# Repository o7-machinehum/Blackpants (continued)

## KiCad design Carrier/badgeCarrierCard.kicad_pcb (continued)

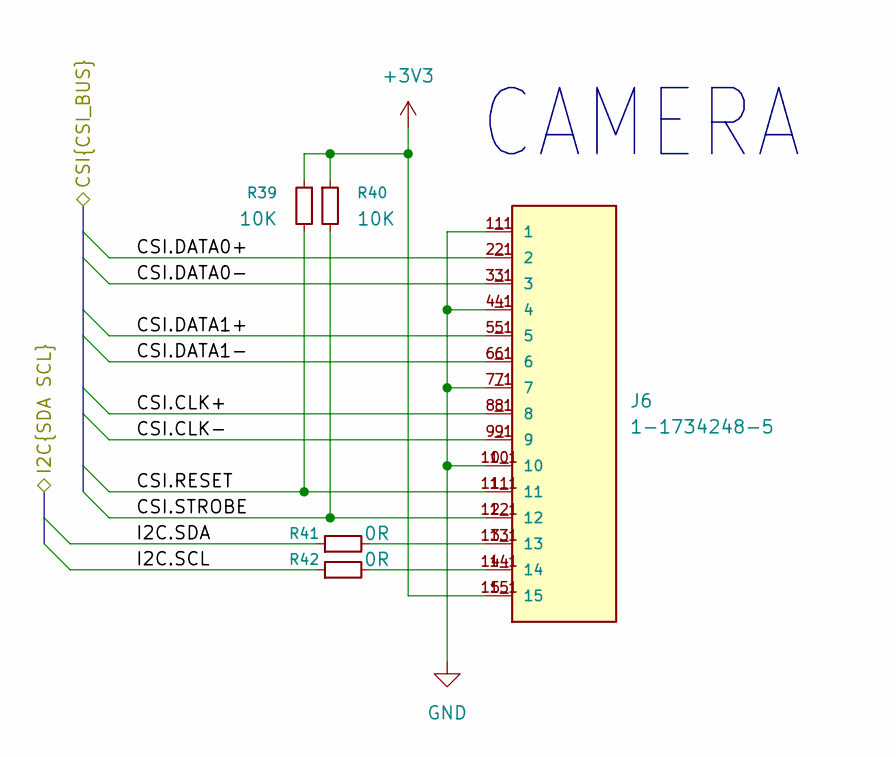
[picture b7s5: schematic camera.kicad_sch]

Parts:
J6: 1-1734248-5; TE_1-1734248-5; PARTREV E1; LCSC C2922285
R39, R40: 10K; R_0402_1005Metric; LCSC C25744
R41, R42: 0R; R_0402_1005Metric; LCSC C17168

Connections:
/CSI.CLK+: J6.8, J6.8_1 (8); also elsewhere on the board
/CSI.CLK-: J6.9, J6.9_1 (9); also elsewhere on the board
/CSI.DATA0+: J6.2, J6.2_1 (2); also elsewhere on the board
/CSI.DATA0-: J6.3, J6.3_1 (3); also elsewhere on the board
/CSI.DATA1+: J6.5, J6.5_1 (5); also elsewhere on the board
/CSI.DATA1-: J6.6, J6.6_1 (6); also elsewhere on the board
/CSI.RESET: J6.11, J6.11_1 (11), R39.2; also elsewhere on the board
/CSI.STROBE: J6.12, J6.12_1 (12), R40.2; also elsewhere on the board
/I2C.SCL: R42.1; also elsewhere on the board
/I2C.SDA: R41.1; also elsewhere on the board
unnamed: J6.13, J6.13_1 (13), R41.2
unnamed: J6.14, J6.14_1 (14), R42.2

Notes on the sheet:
CAMERA

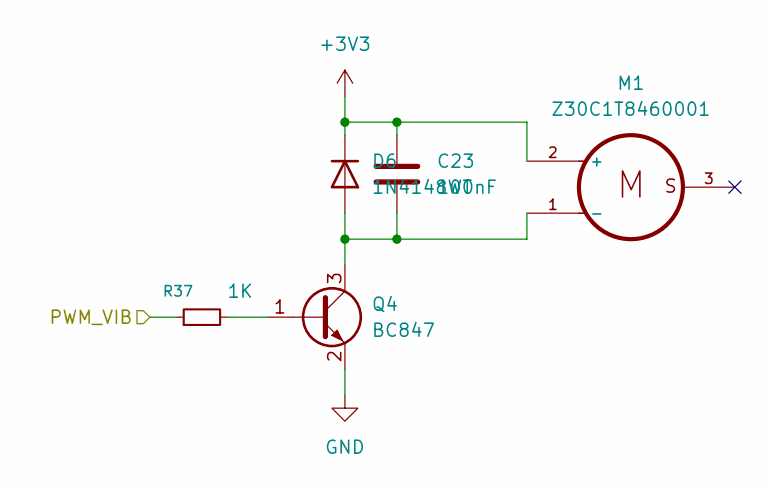
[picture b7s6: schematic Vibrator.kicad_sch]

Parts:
C23: 100nF; C_0805_2012Metric
D6: 1N4148WT; D_SOD-523
M1: Z30C1T8460001; XDCR_Z30C1T8460001
Q4: BC847; SOT-23
R37: 1K; R_0402_1005Metric; LCSC C25900

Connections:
/Vibrator/PWM_VIB: R37.1
unnamed: Q4.1 (B), R37.2

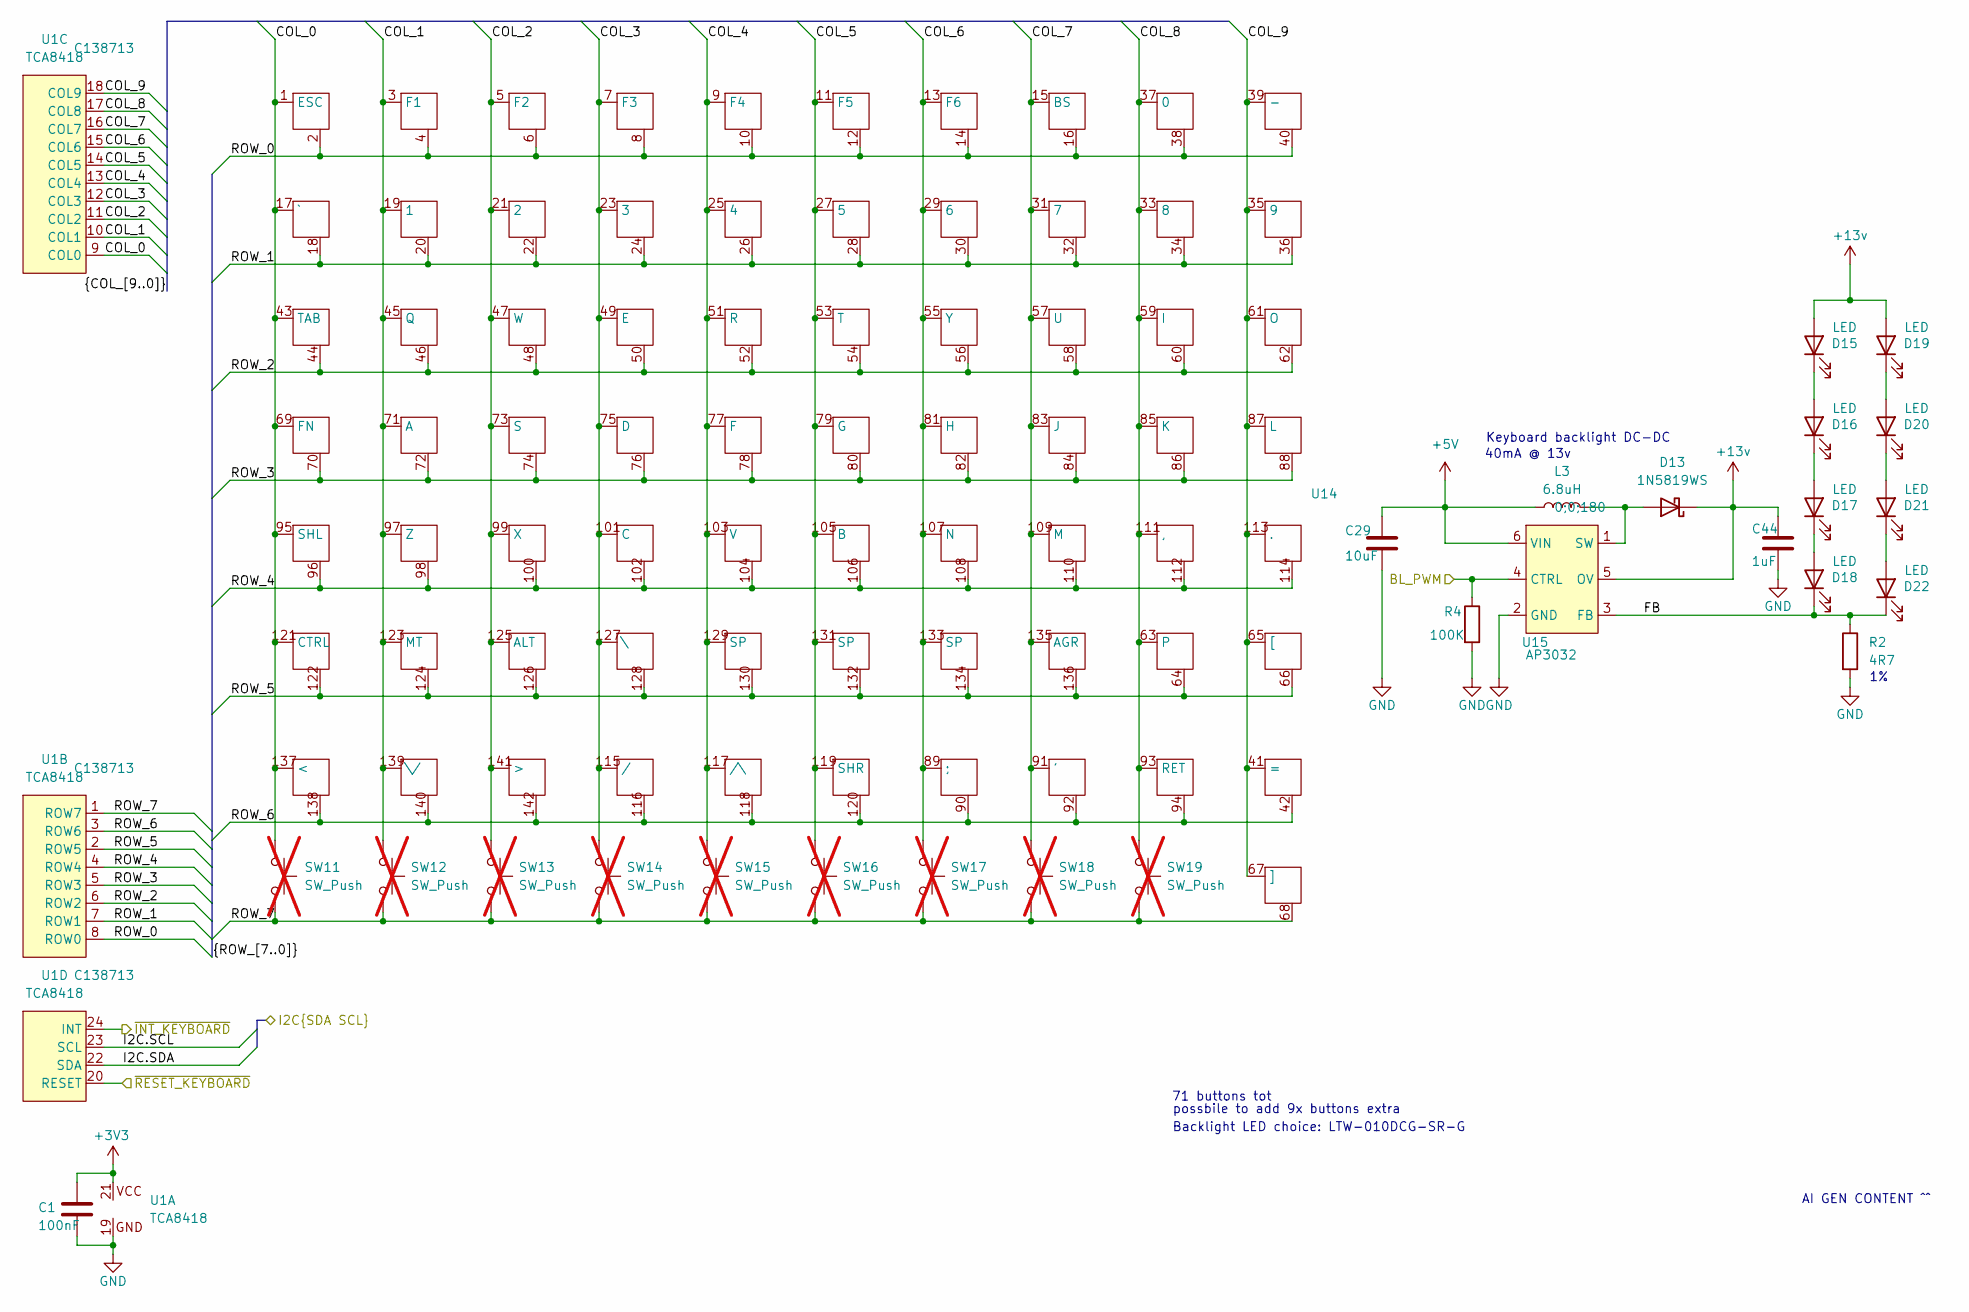
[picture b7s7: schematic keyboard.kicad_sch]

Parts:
C1: 100nF; C_0402_1005Metric; LCSC C307331
C29: 10uF; C_0603_1608Metric; LCSC C96446
C44: 1uF; C_0402_1005Metric; LCSC C52923
D13: 1N5819WS; D_SOD-323; LCSC C191023
D15, D16, D17, D18, D19, D20, D21, D22: LED; LTW-010DCG; LCSC C575429
L3: 6.8uH; L_Vishay_IFSC-1515AH_4x4x1.8mm; LCSC C2050220
R2: 4R7; R_0402_1005Metric; LCSC C25121
R4: 100K; R_0402_1005Metric; LCSC C25741
SW11, SW12, SW13, SW14, SW15, SW16, SW17, SW18, SW19: SW_Push; SW_Push_1P1T_NO_CK_KSC7xxJ; not fitted
U1: TCA8418; QFN50P400X400X80-25N; LCSC C138713
U14: keyboard_arturo182
U15: AP3032; SOT-23-6_Handsoldering; LCSC C264086

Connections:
+13v: C44.1, D13.1 (K), D15.2 (A), D19.2 (A), U15.5 (OV)
/C6_CHIP_PU: U1.20 (RESET); also elsewhere on the board
/I2C.SCL: U1.23 (SCL); also elsewhere on the board
/I2C.SDA: U1.22 (SDA); also elsewhere on the board
/KEYBOARD_BL: R4.1, U15.4 (CTRL); also elsewhere on the board
/Keyboard/COL_0: SW11.1, U1.9 (COL0), U14.1 (ESC), U14.17 (`), U14.43 (TAB), U14.69 (FN), U14.95 (SHL), U14.121 (CTRL), U14.137 (<)
/Keyboard/COL_1: SW12.1, U1.10 (COL1), U14.3 (F1), U14.19 (1), U14.45 (Q), U14.71 (A), U14.97 (Z), U14.123 (MT), U14.139 (\/)
/Keyboard/COL_2: SW13.1, U1.11 (COL2), U14.5 (F2), U14.21 (2), U14.47 (W), U14.73 (S), U14.99 (X), U14.125 (ALT), U14.141 (>)
/Keyboard/COL_3: SW14.1, U1.12 (COL3), U14.7 (F3), U14.23 (3), U14.49 (E), U14.75 (D), U14.101 (C), U14.115 (/), U14.127 (\)
/Keyboard/COL_4: SW15.1, U1.13 (COL4), U14.9 (F4), U14.25 (4), U14.51 (R), U14.77 (F), U14.103 (V), U14.117 (/\), U14.129 (SP)
/Keyboard/COL_5: SW16.1, U1.14 (COL5), U14.11 (F5), U14.27 (5), U14.53 (T), U14.79 (G), U14.105 (B), U14.119 (SHR), U14.131 (SP)
/Keyboard/COL_6: SW17.1, U1.15 (COL6), U14.13 (F6), U14.29 (6), U14.55 (Y), U14.81 (H), U14.89 (;), U14.107 (N), U14.133 (SP)
/Keyboard/COL_7: SW18.1, U1.16 (COL7), U14.15 (BS), U14.31 (7), U14.57 (U), U14.83 (J), U14.91 ('), U14.109 (M), U14.135 (AGR)
/Keyboard/COL_8: SW19.1, U1.17 (COL8), U14.33 (8), U14.37 (0), U14.59 (I), U14.63, U14.85 (K), U14.93 (RET), U14.111 (,)
/Keyboard/COL_9: U1.18 (COL9), U14.35 (9), U14.39 (-), U14.41 (=), U14.61 (O), U14.65 ([), U14.67 (]), U14.87 (L), U14.113 (.)
/Keyboard/FB: D18.1 (K), D22.1 (K), R2.1, U15.3 (FB)
/Keyboard/ROW_0: U1.8 (ROW0), U14.2, U14.4, U14.6, U14.8, U14.10, U14.12, U14.14, U14.16, U14.38, U14.40
/Keyboard/ROW_1: U1.7 (ROW1), U14.18, U14.20, U14.22, U14.24, U14.26, U14.28, U14.30, U14.32, U14.34, U14.36
/Keyboard/ROW_2: U1.6 (ROW2), U14.44, U14.46, U14.48, U14.50, U14.52, U14.54, U14.56, U14.58, U14.60, U14.62
/Keyboard/ROW_3: U1.5 (ROW3), U14.70, U14.72, U14.74, U14.76, U14.78, U14.80, U14.82, U14.84, U14.86, U14.88
/Keyboard/ROW_4: U1.4 (ROW4), U14.96, U14.98, U14.100, U14.102, U14.104, U14.106, U14.108, U14.110, U14.112, U14.114
/Keyboard/ROW_5: U1.2 (ROW5), U14.64, U14.66, U14.122, U14.124, U14.126, U14.128, U14.130, U14.132, U14.134, U14.136
/Keyboard/ROW_6: U1.3 (ROW6), U14.42, U14.90, U14.92, U14.94, U14.116, U14.118, U14.120, U14.138, U14.140, U14.142
/Keyboard/ROW_7: SW11.2, SW12.2, SW13.2, SW14.2, SW15.2, SW16.2, SW17.2, SW18.2, SW19.2, U1.1 (ROW7), U14.68
/Keyboard/~INT_KEYBOARD: U1.24 (INT); also elsewhere on the board
unnamed: D13.2 (A), L3.2, U15.1 (SW)
unnamed: D15.1 (K), D16.2 (A)
unnamed: D16.1 (K), D17.2 (A)
unnamed: D17.1 (K), D18.2 (A)
unnamed: D19.1 (K), D20.2 (A)
unnamed: D20.1 (K), D21.2 (A)
unnamed: D21.1 (K), D22.2 (A)

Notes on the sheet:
71 buttons tot
possbile to add 9x buttons extra
AI GEN CONTENT ^^
Backlight LED choice: LTW-010DCG-SR-G
Keyboard backlight DC-DC
40mA @ 13v

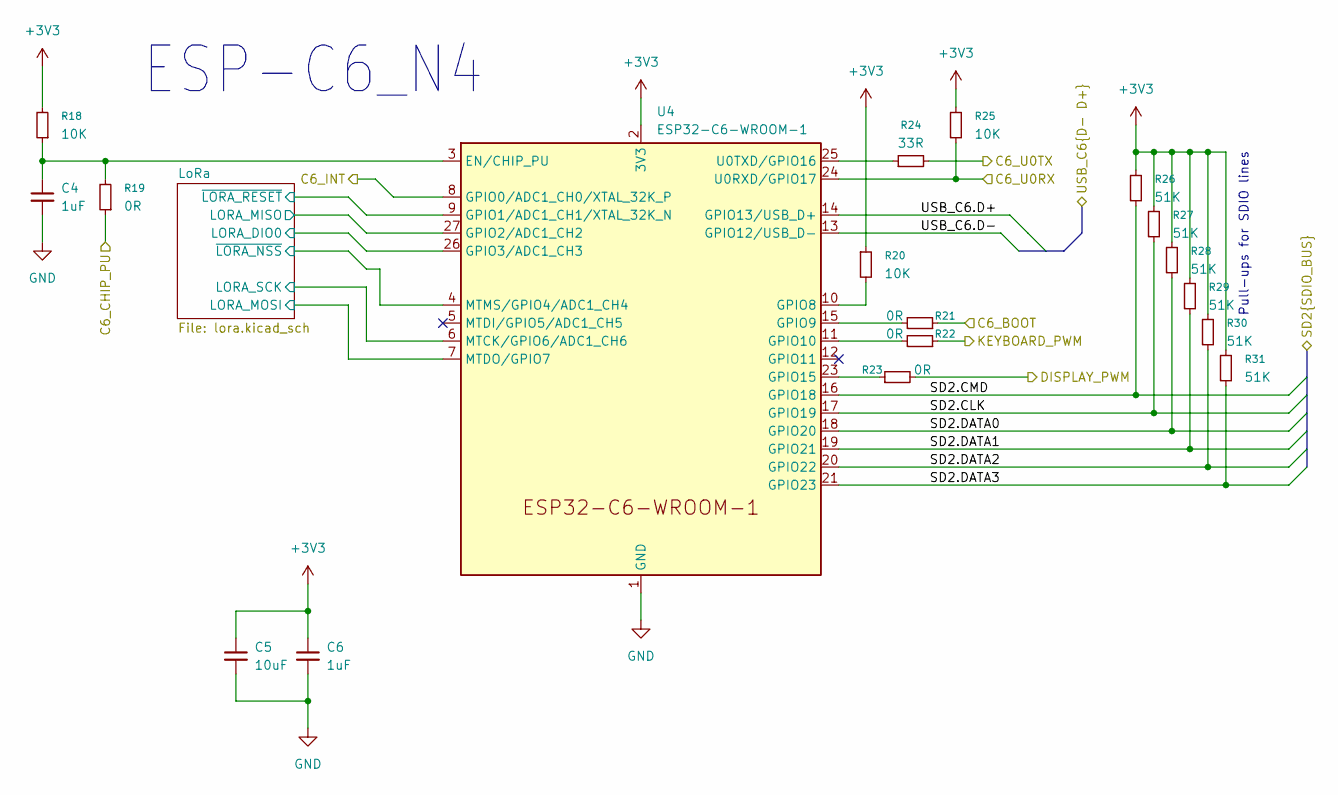
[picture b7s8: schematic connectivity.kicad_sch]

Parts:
C4, C6: 1uF; C_0402_1005Metric; LCSC C52923
C5: 10uF; C_0603_1608Metric; LCSC C96446
R18, R20, R25: 10K; R_0402_1005Metric; LCSC C25744
R19, R21: 0R; R_0402_1005Metric; LCSC C17168
R22: 0R; R_0603_1608Metric; LCSC C17168
R23: 0R; R_0603_1608Metric; LCSC C15402
R24: 33R; R_0402_1005Metric; LCSC C25105
R26, R27, R28, R29, R30, R31: 51K; R_0402_1005Metric; LCSC C25794
U4: ESP32-C6-WROOM-1; LCSC C5366877

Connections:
/C6_BOOT: R21.1; also elsewhere on the board
/C6_CHIP_PU: R19.1; also elsewhere on the board
/C6_INT: U4.8 (GPIO0/ADC1_CH0/XTAL_32K_P); also elsewhere on the board
/C6_RX: R25.1, U4.24 (U0RXD/GPIO17); also elsewhere on the board
/C6_TX: R24.2; also elsewhere on the board
/Connectivity (C6 + LoRa)/LoRa/LORA_DIO0: U4.26 (GPIO3/ADC1_CH3); also elsewhere on the board
/Connectivity (C6 + LoRa)/LoRa/LORA_MISO: U4.27 (GPIO2/ADC1_CH2); also elsewhere on the board
/Connectivity (C6 + LoRa)/LoRa/LORA_MOSI: U4.7 (MTDO/GPIO7); also elsewhere on the board
/Connectivity (C6 + LoRa)/LoRa/LORA_SCK: U4.6 (MTCK/GPIO6/ADC1_CH6); also elsewhere on the board
/Connectivity (C6 + LoRa)/LoRa/~LORA_NSS: U4.4 (MTMS/GPIO4/ADC1_CH4); also elsewhere on the board
/Connectivity (C6 + LoRa)/LoRa/~LORA_RESET: U4.9 (GPIO1/ADC1_CH1/XTAL_32K_N); also elsewhere on the board
/Connectivity (C6 + LoRa)/SD2.CLK: R27.1, U4.17 (GPIO19); also elsewhere on the board
/Connectivity (C6 + LoRa)/SD2.CMD: R26.1, U4.16 (GPIO18); also elsewhere on the board
/Connectivity (C6 + LoRa)/SD2.DATA0: R28.1, U4.18 (GPIO20); also elsewhere on the board
/Connectivity (C6 + LoRa)/SD2.DATA1: R29.1, U4.19 (GPIO21); also elsewhere on the board
/Connectivity (C6 + LoRa)/SD2.DATA2: R30.1, U4.20 (GPIO22); also elsewhere on the board
/Connectivity (C6 + LoRa)/SD2.DATA3: R31.1, U4.21 (GPIO23); also elsewhere on the board
/Connectivity (C6 + LoRa)/USB_C6.D+: U4.14 (GPIO13/USB_D+); also elsewhere on the board
/Connectivity (C6 + LoRa)/USB_C6.D-: U4.13 (GPIO12/USB_D-); also elsewhere on the board
/DISPLAY_BL: R23.2; also elsewhere on the board
/KEYBOARD_BL: R22.1; also elsewhere on the board
unnamed: C4.1, R18.1, R19.2, U4.3 (EN/CHIP_PU)
unnamed: R20.2, U4.10 (GPIO8)
unnamed: R21.2, U4.15 (GPIO9)
unnamed: R22.2, U4.11 (GPIO10)
unnamed: R23.1, U4.23 (GPIO15)
unnamed: R24.1, U4.25 (U0TXD/GPIO16)

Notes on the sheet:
Pull-ups for SDIO lines
ESP-C6_N4

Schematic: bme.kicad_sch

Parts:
C13, C14: 100nF; C_0402_1005Metric; LCSC C307331
U7: BME680; Bosch_LGA-8_3x3mm_P0.8mm_ClockwisePinNumbering; LCSC C125972

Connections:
/I2C.SCL: U7.4 (SCK); also elsewhere on the board
/I2C.SDA: U7.3 (SDI); also elsewhere on the board

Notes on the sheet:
BME690

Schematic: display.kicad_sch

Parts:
C11, C12: 100nF; C_0402_1005Metric; LCSC C307331
C30, C31, C32: 10uF; C_0603_1608Metric; LCSC C96446
C46: 1uF; C_0402_1005Metric; LCSC C52923
D14: 1N5819WS; D_SOD-323; LCSC C191023
J9: Conn_01x30; AFC30; LCSC C262569
L4: 6.8uH; L_Vishay_IFSC-1515AH_4x4x1.8mm; LCSC C2050220
Q2: AO3400A; SOT-23; LCSC C20917
R34: 100K; R_0402_1005Metric; LCSC C25741
R35: 4R7; R_0402_1005Metric; LCSC C25121
R36: 10K; R_0402_1005Metric; LCSC C25744
R45: 0R; R_0603_1608Metric; LCSC C15402
U3: AMS1117-1.8; SOT-223-3_TabPin2; LCSC C6185
U16: AP3032; SOT-23-6_Handsoldering; LCSC C264086

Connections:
+1V8: C11.1, C32.1, J9.9, R36.1, U3.2 (VO)
/DISPLAY_BL: R45.2; also elsewhere on the board
/DSI.CLK+: J9.20; also elsewhere on the board
/DSI.CLK-: J9.19; also elsewhere on the board
/DSI.DATA0+: J9.14; also elsewhere on the board
/DSI.DATA0-: J9.13; also elsewhere on the board
/DSI.DATA1+: J9.17; also elsewhere on the board
/DSI.DATA1-: J9.16; also elsewhere on the board
/DSI.RESET: Q2.1 (G); also elsewhere on the board
/Display/ADJ_BL_KEYBOARD_DISPLAY: R34.1, R45.1, U16.4 (CTRL); also elsewhere on the board
/Display/FB: J9.29, J9.30, R35.1, U16.3 (FB)
unnamed: D14.2 (A), L4.2, U16.1 (SW)
unnamed: C46.1, D14.1 (K), J9.28, U16.5 (OV)
unnamed: J9.11, Q2.3 (D), R36.2

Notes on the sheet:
40mA @ 13v
Display backlight DC-DC
DISPAY

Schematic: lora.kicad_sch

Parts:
C7: 100nF; C_0402_1005Metric; LCSC C307331
C8: 10uF; C_0603_1608Metric; LCSC C96446
J5: SMA-J-P-X-RA-TH1; SAMTEC_SMA-J-P-X-RA-TH1; PARTREV K
U5: Ai-Thinker-Ra-01H; Ai-Thinker-Ra-01-LoRa; LCSC C503593

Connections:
/Connectivity (C6 + LoRa)/LoRa/ANTENNA: J5.1, U5.1 (ANT)
/Connectivity (C6 + LoRa)/LoRa/LORA_DIO0: U5.5 (DIO0); also elsewhere on the board
/Connectivity (C6 + LoRa)/LoRa/LORA_MISO: U5.13 (MISO); also elsewhere on the board
/Connectivity (C6 + LoRa)/LoRa/LORA_MOSI: U5.14 (MOSI); also elsewhere on the board
/Connectivity (C6 + LoRa)/LoRa/LORA_SCK: U5.12 (SCK); also elsewhere on the board
/Connectivity (C6 + LoRa)/LoRa/~LORA_NSS: U5.15 (~NSS); also elsewhere on the board
/Connectivity (C6 + LoRa)/LoRa/~LORA_RESET: U5.4 (~RESET); also elsewhere on the board

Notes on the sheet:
LORA

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
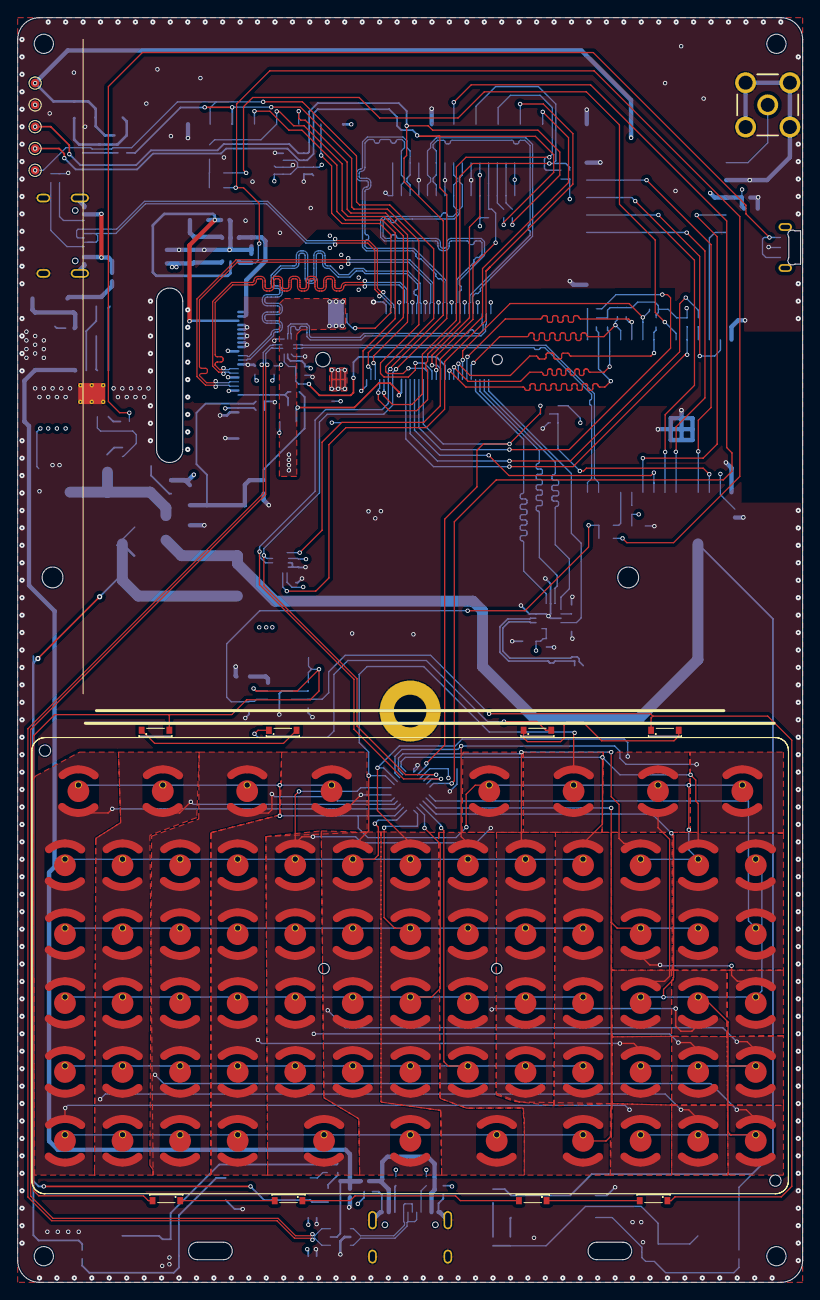
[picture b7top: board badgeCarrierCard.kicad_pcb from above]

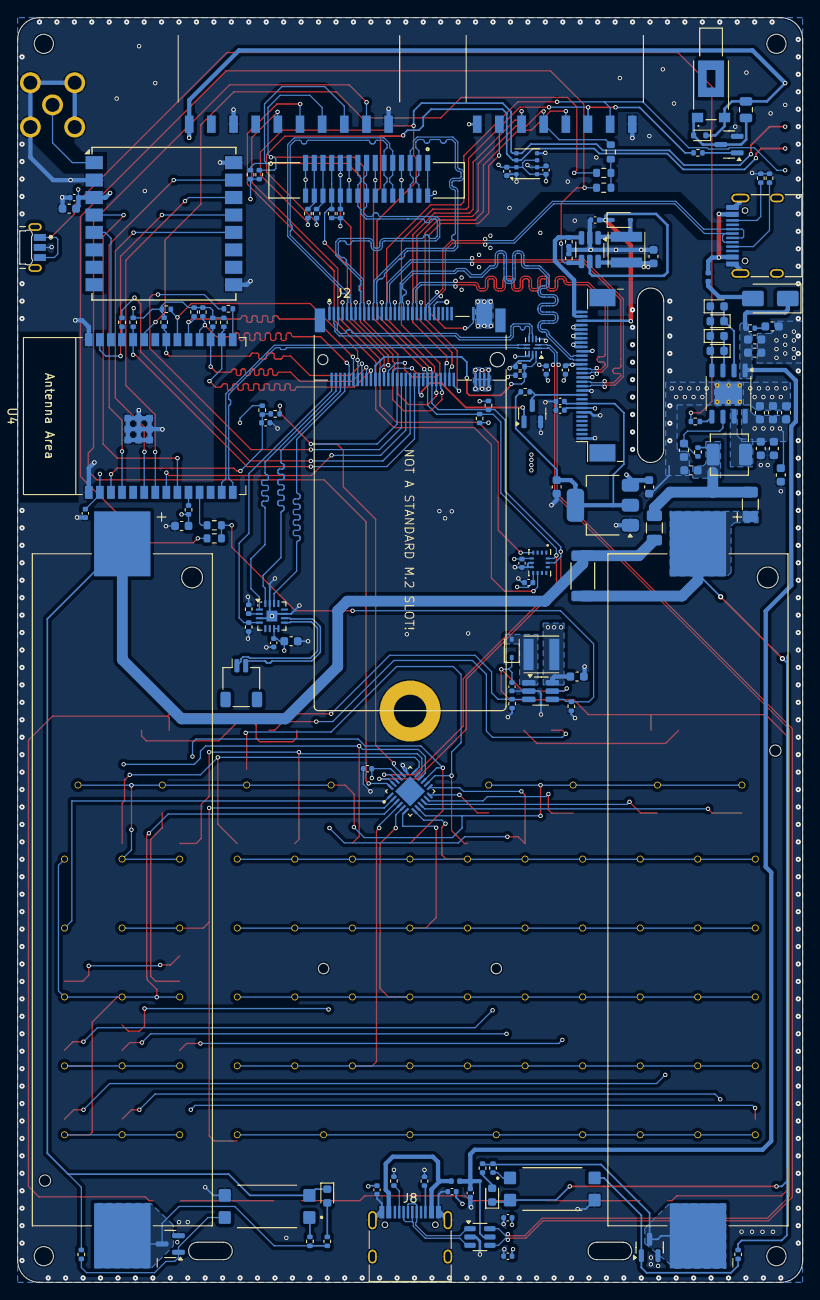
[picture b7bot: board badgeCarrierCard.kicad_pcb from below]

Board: 4 copper layers, 90.0 x 145.0 mm, 156 parts (136 on the bottom side), 138 nets.

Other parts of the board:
C23#2: 100nF; C_0805_2012Metric
R40#2: 470; R_0402_1005Metric
U10#2: EL817S1C; SOIC254P1030X390-4N

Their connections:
unnamed 92: U10#2.2; also elsewhere on the board
unnamed 93: R40#2.2; also elsewhere on the board
unnamed 119: U10#2.4; also elsewhere on the board
unnamed 122: U10#2.1; also elsewhere on the board

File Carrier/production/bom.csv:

Comment,Designator,Footprint,LCSC
5.1K,"R1,R3,R11,R12",Resistor_SMD:R_0402_1005Metric,C25905
MountingHole_Pad,H5,Standoff:Standoff,C19626599
4.7K,"R5,R6,R7,R8",Resistor_SMD:R_0402_1005Metric,C25900
120Ω@100MHz,"FB1,FB2",Inductor_SMD:L_0402_1005Metric,C76891
Conn_01x10,J7,badge:SMD_10,C5142243
0R,R45,Resistor_SMD:R_0603_1608Metric,C15402
TPSGM7227YUWQ10G,U11,Package_DFN_QFN:UQFN-10_1.4x1.8mm_P0.4mm,C42379165
100nF,"C1,C7,C10,C11,C12,C13,C14,C15,C16,C23,C45,C47,C48,C49,C50,C51,C52",Capacitor_SMD:C_0402_1005Metric,C307331
0R,"R19,R41,R42,R53",Resistor_SMD:R_0402_1005Metric,C17168
10K,"R9,R15,R18,R20,R25,R32,R36,R39,R40",Resistor_SMD:R_0402_1005Metric,C25744
Conn_01x08,J3,badge:SMD_8,C5142241
USB_C_Receptacle_USB2.0_16P,"J1,J8",Connector_USB:USB_C_Receptacle_HRO_TYPE-C-31-M-12,C165948
MDT420M02003,J2,MDT420M02003:AMPHENOL_MDT420M02003,C410529
LED,"D2,D3,D4,D5",Diode_SMD:D_0603_1608Metric,C2286
LED,"D7,D8",LED_SMD:LED_0603_1608Metric,C2286
EL817S1C,"U9,U10",EL817:SOIC254P1030X390-4N,C2912100
SS54,D1,Diode_SMD:D_SMA,C22452
22uF,"C18,C19,C20,C21,C22",Capacitor_SMD:C_0603_1608Metric,C59461
200,R13,Resistor_SMD:R_2010_5025Metric,C19610
AO3400A,"Q1,Q2,Q3",Package_TO_SOT_SMD:SOT-23,C20917
IP5306,U2,Package_SO:HSOP-8-1EP_3.9x4.9mm_P1.27mm_EP2.41x3.1mm_ThermalVias,C181692
USBLC6-2SC6,U12,Package_TO_SOT_SMD:SOT-23-6,C7519
PTS847MM160LSMTR2_LFS,PWR_BUTTON1,PTS847MM160LSMTR2_LFS:SW_PTS847MM160SMTR2_LFS,C2927780
1K,"R37,R43,R48",Resistor_SMD:R_0402_1005Metric,C11702
470,"R46,R50",Resistor_SMD:R_0402_1005Metric,C25117
Polyfuse,"F1,F2",Fuse:Fuse_1206_3216Metric,C20988
10uF,"C2,C3,C5,C8,C9,C17,C29,C30,C31,C32",Capacitor_SMD:C_0603_1608Metric,C96446
1uH,L1,Inductor_SMD:L_Changjiang_FXL0420,C32712969
18650 Cell,"BT1,BT2",BH-18650-B1BA002:BH-18650-B1BA002,C2988620
0.5,R17,Resistor_SMD:R_0402_1005Metric,C332662
150,"R38,R47",Resistor_SMD:R_0402_1005Metric,C25082
2,R14,Resistor_SMD:R_0402_1005Metric,C25157
BMI270,U8,BMI270:XDCR_BMI270,C2836813
100K,"R4,R33,R34",Resistor_SMD:R_0402_1005Metric,C25741
Speaker,LS1,badge:JST_PH_S2B-PH-K_1x02_P2.00mm_Horizontal,C160402
MAX98357A,U6,Package_DFN_QFN:TQFN-16-1EP_3x3mm_P0.5mm_EP1.23x1.23mm,C910544
1-1734248-5,J6,1-1734248-5:TE_1-1734248-5,C2922285
6.8R,R54,Resistor_SMD:R_0402_1005Metric,C11702
1N4148WT,D6,Diode_SMD:D_SOD-523,C232841
Z3OC1T8219731,M1,Z3OC1T8219731,C2894731
BC847,Q4,Package_TO_SOT_SMD:SOT-23,C2926209
LED,"D15,D16,D17,D18,D19,D20,D21,D22",keyboard_leds:LTW-010DCG,C575429
TCA8418,U1,TCA8418RTWR:QFN50P400X400X80-25N,C138713
~,U14,keyboard:keyboard_arturo182,
AP3032,"U15,U16",Package_TO_SOT_SMD:SOT-23-6_Handsoldering,C264086
6.8uH,"L3,L4",Inductor_SMD:L_Vishay_IFSC-1515AH_4x4x1.8mm,C2050220
1uF,"C4,C6,C44,C46",Capacitor_SMD:C_0402_1005Metric,C52923
1N5819WS,"D13,D14",Diode_SMD:D_SOD-323,C191023
4R7,"R2,R35",Resistor_SMD:R_0402_1005Metric,C25121
51K,"R26,R27,R28,R29,R30,R31",Resistor_SMD:R_0402_1005Metric,C25794
33R,"R21,R22,R23,R24",Resistor_SMD:R_0402_1005Metric,C25105
ESP32-C6-WROOM-1,U4,PCM_Espressif:ESP32-C6-WROOM-1,C5366877
Ai-Thinker-Ra-01H,U5,RF_Module:Ai-Thinker-Ra-01-LoRa,C503593
BME680,U7,Package_LGA:Bosch_LGA-8_3x3mm_P0.8mm_ClockwisePinNumbering,C125972
Conn_01x30,J9,FPC:AFC30,C262569
AMS1117-1.8,U3,Package_TO_SOT_SMD:SOT-223-3_TabPin2,C6185

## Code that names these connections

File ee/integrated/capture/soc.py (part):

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        local_nets={'X32KIN','X32KOUT','DXIN','DXOUT'})
    p=s.symbol('Device:Crystal_GND24','Y201','24MHz / CL20pF / 20ppm',195.58,45.72,
               footprint='Crystal:Crystal_SMD_3225-4Pin_3.2x2.5mm')
    s.wire(p['1'],(167.64,45.72));s.label('DXIN',(167.64,45.72),180)
    s.wire(p['3'],(220.98,45.72))
    for n in ['2','4']:
        gx=190.5 if n=='2' else 200.66
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
    s=Sheet('a523_gpio.kicad_sch','A523 - SD card, console and unused storage IO')
    s.text('Boot SD / UART0 console / GPIO',20.32,15.24,2.032)
    soc(s,4,83.82,40.64,{'PB9':'UART0_TX','PB10':'UART0_RX','PB4':'A523_I2C1_SCL','PB5':'A523_I2C1_SDA','PB11':'USB0_VBUS_DET',
        'PB7':'LCD_RST','PB8':'LCD_PWM','PB6':'LCD_TE','PF0':'SD0_D1','PF1':'SD0_D0','PF2':'SD0_CLK_SOC',
        'PF3':'SD0_CMD','PF4':'SD0_D3','PF5':'SD0_D2','PF6':'SD0_DET','VCC-PC':'VCC_3V3'},local_nets={'SD0_CLK_SOC'})
    cap(s,'C261','100nF','VCC_3V3',182.88,45.72)
    s.passive('R','R203','33',182.88,83.82,'SD0_CLK','SD0_CLK_SOC',True,local_nets={'SD0_CLK_SOC'})
    s.text('UART0: PB9 / PB10, mux 2.\nSDC0: PF0..PF5, mux 2; PF6 detect.\nLCD PWM: PB8 mux 6. Reset / TE: GPIO.\nPB11: divided USB0 VBUS detect.\nI2C1: expansion header with 3.3V pull-ups.',152.4,116.84)
    s.save()

    s=Sheet('a523_display_io.kicad_sch','A523 - DSI display IO')
    s.text('Two-lane DSI0 to the existing display connector',20.32,15.24,2.032)
    soc(s,5,83.82,40.64,{'PD0':'DSI_D0P','PD1':'DSI_D0N','PD2':'DSI_D1P','PD3':'DSI_D1N',
        'PD4':'DSI_CKP','PD5':'DSI_CKN','VCC-PD':'VCC_3V3','VCC-LVDS0':'VCC_1V8','VCC-PE':'VCC_PE'})
    bank(s,262,'VCC_3V3',['10uF','100nF'],172.72,45.72)
    cap(s,'C264','100nF','VCC_1V8',177.8,83.82)
    cap(s,'C265','100nF','VCC_PE',228.6,83.82)
    s.text('PD0..PD5: DSI0 mux 4. Clock = PD4/PD5.\nPD6..PD9 unused with the two-lane panel.\nFollow panel and A523 routing constraints.\nPE camera bank remains disabled.',152.4,116.84)
    s.save()

    s=Sheet('a523_wifi_io.kicad_sch','A523 - Wi-Fi, Bluetooth and DDR strap GPIO')
    s.text('SDIO1 / UART1 / DDR parameter straps',20.32,15.24,2.032)
    soc(s,6,83.82,40.64,{'PG0':'SD1_CLK_SOC','PG1':'SD1_CMD','PG2':'SD1_D0','PG3':'SD1_D1',
        'PG4':'SD1_D2','PG5':'SD1_D3','PG6':'BT_RXD','PG7':'BT_TXD','PG8':'BT_CTS_N','PG9':'BT_RTS_N',
        'VCC-PG':'VCC_PG','PH16':'DDR_ID0','PH17':'DDR_ID1',
        'PH0':'WL_REG_ON','PH1':'WL_HOST_WAKE','PH2':'BT_RESET_N','PH3':'BT_WAKE','PH4':'BT_HOST_WAKE'},local_nets={'SD1_CLK_SOC','DDR_ID0','DDR_ID1'})
    cap(s,'C266','100nF','VCC_PG',182.88,40.64)
    for i,net in enumerate(['DDR_ID0','DDR_ID1']):
        x=165.1+i*63.5
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        s.wire(hi['2'],lo['1']);s.label(net,(x,137.16));s.junction((x,137.16))
        s.wire(hi['1'],(x,120.65));s.power('VCC_AVCC',(x,120.65))
        s.wire(lo['2'],(x,156.21));s.power('GND',(x,156.21))
    s.text('BOOT_ADC: STD 10k / 3.9k, SD boot available.\nDDR_ADC: 0.383V; PH16/PH17 = 0/0 selects set 1.\nBuild set 1 for Nanya 16Gb LPDDR4.\nUnused audio / ADC IO is unconnected.\nKeep audio and headphone blocks disabled.',20.32,175.26,1.016)
    s.save()


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
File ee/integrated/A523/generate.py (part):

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                if name == "TEST":
                    assert b == "AE1"
                    b, correction = "AE11", "TEST: AE1 -> AE11"
                if re.fullmatch(r"PB1[0-4]", b):
                    assert name == b
                    b = "L" + str(15 + int(name[2:]))
                    correction = f"{name}: invalid ball {name} -> {b}"
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
def electrical_type(pin):
    # Internal regulator/charge-pump outputs and remote supply-sense taps.
    if pin["name"] in {"ALDO-OUT", "CPVEE", "CPVDD"}:
        return "power_out"
    if pin["name"] == "VRP":
        return "output"  # Datasheet function table: internal analog reference.
    if pin["name"] in {"PCIE-REF-CLKP", "PCIE-REF-CLKN"}:
        return "input"  # Dedicated reference-clock inputs; grounded when unused.
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
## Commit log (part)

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2025-04-08 Add empty README
2025-06-05 MIT License
2025-06-08 Updated module, now with uSD
2025-06-08 Fixed mistakes from prototype 1
2025-06-08 Prototype 2 files
2025-06-08 Push change, allready fix usb mux
2025-06-08 fix annotation
2025-06-08 fix: sync schematic prot3 and v2.5
2025-06-08 fix: add missing ocoupler lib
2025-06-08 push back to adam:DDD
2025-06-08 push resistor name
2025-06-08 push final
2025-06-08 fix: implement balancer changes
2025-06-08 cleaning routes and positions
2025-06-08 SIlk and logo added
2025-06-08 schematic update names
2025-06-08 Resistor value update c6
2025-06-08 adjust footprint W395HDC001-A
2025-06-08 EMF Lora and Jays LCD footprint added:-)
2025-06-08 small via changes
2025-06-08 chore: DRC fixes
2025-06-08 fix: add ordercodes for production files
2025-06-08 fix: component positions & 3dmodels
2025-06-08 push
2025-06-08 Funny silkscreen and clearing up for protuction
2025-06-08 fix: drc
2025-06-08 fix: cleanup silkscreen labels
2025-06-08 feat: add leds and 3dmodels
2025-06-08 fix: revert m2 changes
2025-06-08 chore: repo cleanup
2025-06-08 chore: generate production files
2025-06-08 chore: lib cleanup
2025-06-08 fix: last minute resistor changes
2025-06-08 front panel pads update push to jay,
2025-06-08 STOCK LCSC vibr, and silkscreen changes
2025-06-08 pad changing
2025-06-08 update PCB from schematics
2025-06-08 last pogo changes
2025-06-08 testpads footprints
2025-06-08 fix: standoff part number
2025-06-08 fix: new smd footprint for button
2025-06-08 fix: change button part number
2025-06-08 fix: vibrator library linking & 3dmodel
2025-06-08 fix: drc errors & prod files
2025-06-09 Final Commit Yeahh
2025-06-09 Final Push M.2
2025-06-09 fix: add warning + prod files
2025-06-10 fix: speaker connector from SH-1.0 to PH-2.0
2025-06-10 silscreen fix
2025-06-10 chore: generate prod files
2025-06-10 chore: regenerate prod files to include bom
2025-06-10 Edit README.md
2025-06-11 Fixed esp_en issue
2025-06-11 traces with changes
2025-06-13 chore: cleanup repository & add build system
2025-06-13 chore: make kikit commands executable with system package
2025-06-14 chore: prepare CI env image
2025-06-14 chore: set dependencies to on_success
2025-06-14 chore: add package exports
2025-06-14 fix: carrier drc
2025-06-14 norun:chore: fix tag releases in pipeline
2025-06-14 norun:chore: mark steps before package as needed and use one export pkg
2025-06-15 fix: cleanup m2 project structure and schematic
2025-06-15 norun: fix: change disp. backlight feedback resistance
2025-06-16 Moved lcd screen connector for new screen, corrected LCSC partnumbers
2025-06-19 Fixed lane skew
2025-06-19 minor silkscreen adjustment and pogo pins
2025-06-19 fix: set pogo pins to DNP
2025-06-19 Fixed DRC
2025-06-24 Impedance matching new stackup
2025-07-17 Add spacer
2025-07-23 ADD all schematic pdf files and ADD lasercut spacer files
2025-07-23 ADD README.md for Spacer folder
2025-07-25 Pushing Addons to Gitlab
    Four addons to inspire fun and hacking.
2025-07-25 Middle part spacer
2025-07-26 Flipped SAO connectors, to match v1.69bis spec
    Also
    - Re-routed connections to the SAO connectors
    - Teaked clearance for fill and moved a few traces for better GND and VCC coverage
    - Changed 3v to 3v3 silkscreen on connector to badge
    - Changed 3D model to be badge side keyed SAO connector
2025-07-26 Add twopart spacer design, restore stucture of the Spacer folder
2025-07-26 Fix README for new files.
2025-07-26 Add case and README.
2025-07-30 Production spacer OD5 ID3 H3
    This is the spacers we use for assembly of the WHY badge.
2025-07-30 Adding the full spacer design with LoRa antenna cutout for WHY2025 badge
    This is the full spacer with a cutout for the LoRa antanna.
2025-07-30 Fixed SD det line reconnected to P4
    There was an error in the production release. This fixes the problem found after pcb went to production. In case you want to reuse this, with this change the SD card change detection works as intente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
2025-07-30 Fix typo in schematic for FLASH
    Correction on schematic from FALSH to FLASH. Simple typo correction, nothing more.
2025-08-01 Update readme file, with discord en telegram hub
    A hub for WHY2025 badge activities: mods, hacks, 3D prints, and new ideas to customize your badge experience.
2025-08-02 Case design improvements for 3D printing
2025-08-08 Added alternative slim case
2025-08-10 Updated readme for slim case
2025-08-10 Main
2025-08-12 update pogopin height to match spacer thickness
    (cherry picked from commit 37a83f917e718d9e4aeca91f363322eda9a9839c)
2025-08-12 add component information to README
    (cherry picked from commit 1f92f649f97ca2c8958248cc6e32acef018db8b2)
2025-08-21 Started ripping parts out
2025-08-21 Rotated the 18650 cell / Wired it in. Wired out circuitry, placed flipper zero headers down.
2025-09-02 Pulled out some stuff I don't need.
2025-09-15 Working away on the board.
2025-09-15 Rename
2025-09-15 Renamed
2025-09-15 Added step files back
2025-09-16 Passing DRC
2025-09-18 R0.1 candidate
2025-09-18 Added PDF
2026-01-28 Add Docker support for self-contained builds
    - Add Dockerfile based on official kicad/kicad:9.0 image
    - Add docker-compose.yml for easy local development
    - Update Makefile to work with Docker and locally
    - Add Docker setup instructions to README
    - Installs kikit and make for hardware build pipeline
